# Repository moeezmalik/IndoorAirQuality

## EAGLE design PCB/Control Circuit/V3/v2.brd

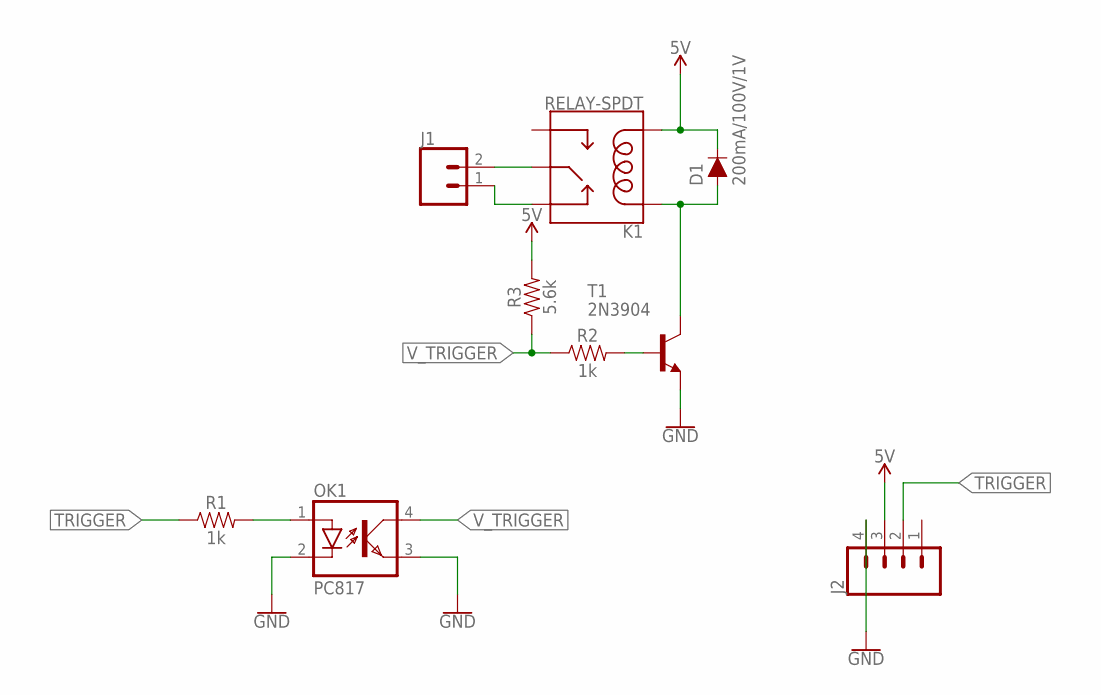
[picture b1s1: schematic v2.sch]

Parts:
D1: 200mA/100V/1V; DIODE-1N4148-KIT
J1: CONN_025MM; SCREWTERMINAL-5MM-2
J2: CONN_04; 1X04
K1: RELAY-SPDT; RELAY_G5LE
OK1: PC817; DIL04
R1, R2: 1k; AXIAL-0.3
R3: 5.6k; AXIAL-0.3
T1: 2N3904; TO92

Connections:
5V: D1.C, J2.3, K1.5 (COIL2), R3.P$2 (2)
GND: J2.4, OK1.2 (C), OK1.3 (EMIT), T1.3 (E)
unnamed: OK1.1 (A), R1.P$2 (2)
unnamed: J1.2, K1.1 (MAIN)
unnamed: J1.1, K1.4 (NC)
unnamed: R2.P$2 (2), T1.2 (B)
unnamed: D1.A, K1.2 (COIL1), T1.1 (C)
TRIGGER: J2.2, R1.P$1 (1)
V_TRIGGER: OK1.4 (COL), R2.P$1 (1), R3.P$1 (1)

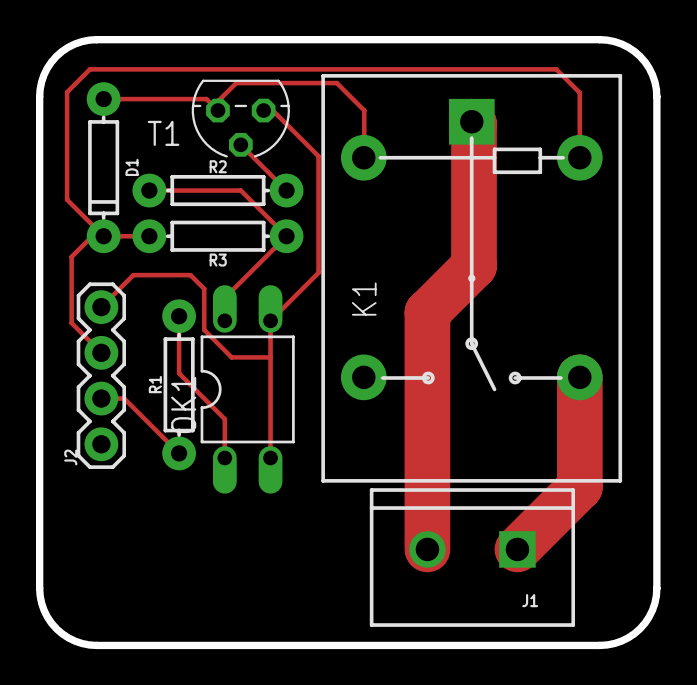
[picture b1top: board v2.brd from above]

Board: 2 copper layers, 34.3 x 33.7 mm, 9 parts (0 on the bottom side), 9 nets.

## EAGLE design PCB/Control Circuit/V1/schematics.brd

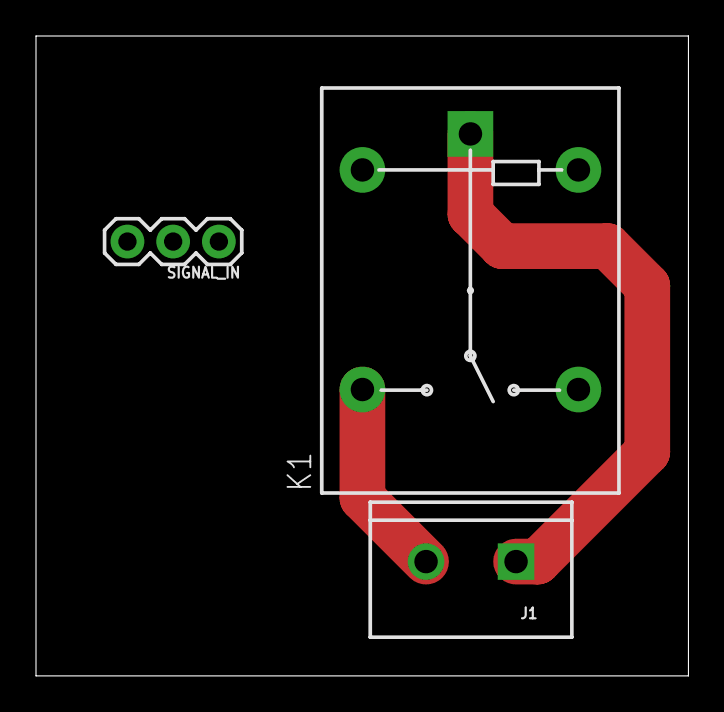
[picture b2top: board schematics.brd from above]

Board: 2 copper layers, 36.2 x 35.5 mm, 3 parts (0 on the bottom side), 3 nets.

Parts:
J1: SCREWTERMINAL-5MM-2
K1: RELAY-SPDT; RELAY_G5LE
SIGNAL_IN: 1X03

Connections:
5V: K1.5, SIGNAL_IN.2
unnamed: J1.2, K1.3
unnamed: J1.1, K1.1

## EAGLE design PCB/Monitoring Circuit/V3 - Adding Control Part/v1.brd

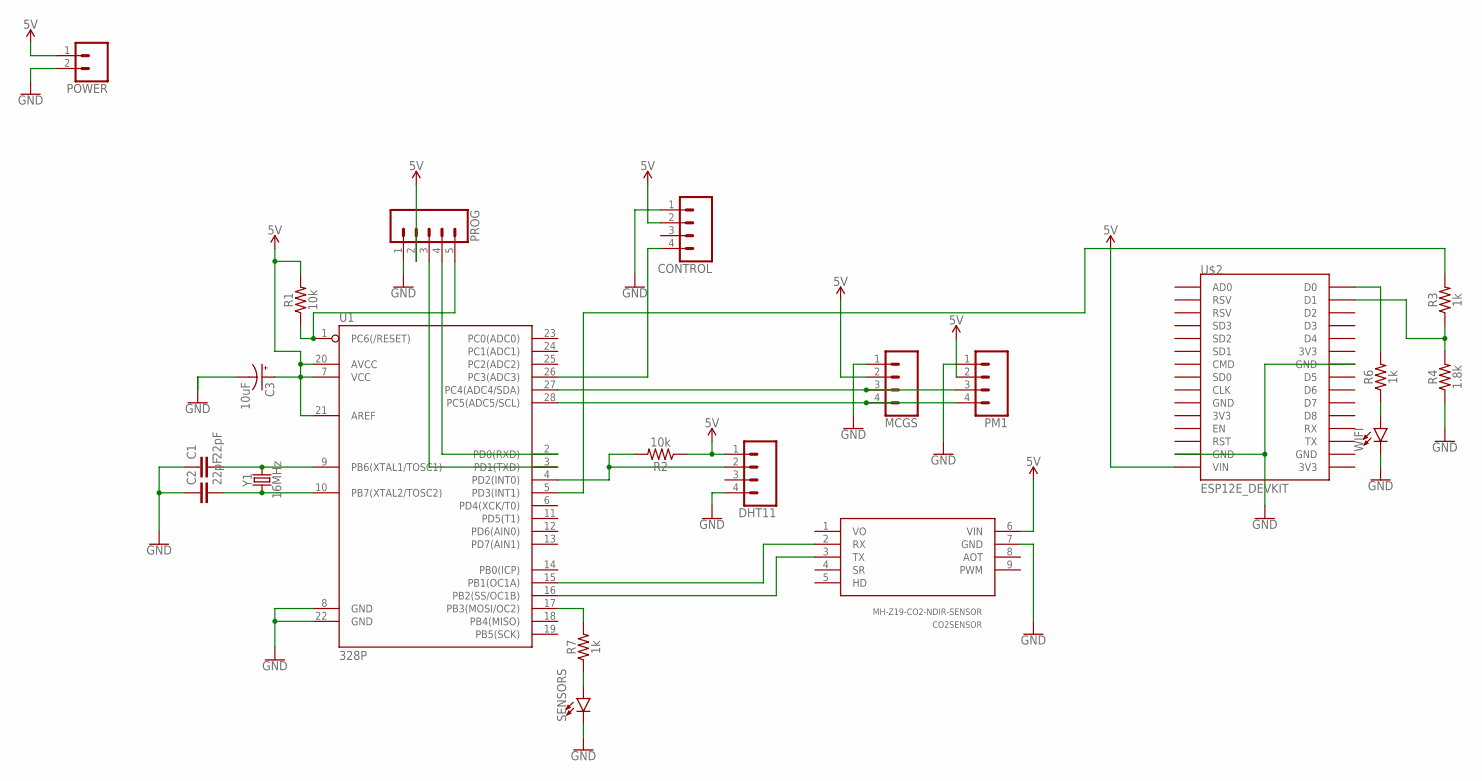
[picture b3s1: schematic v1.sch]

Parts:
C1, C2: 22pF; CAP-PTH-2.54
C3: 10uF; CPOL-RADIAL-2.5MM-5MM
CO2SENSOR: MH-Z19-CO2-NDIR-SENSOR; MH-Z19
CONTROL: CONN_04; 1X04
DHT11: CONN_04; 1X04
MCGS: CONN_04; 1X04
PM1: CONN_04; 1X04
POWER: CONN_02; 1X02
PROG: CONN_05; 1X05
R1, R2: 10k; AXIAL-0.3
R3, R6, R7: 1k; AXIAL-0.3
R4: 1.8k; AXIAL-0.3
SENSORS: LED1206; LED-1206
U1: 328P; DIP28
U$2: ESP12E_DEVKIT
WIFI: LED1206; LED-1206
Y1: 16MHz; HC49US

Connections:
5V: C3.1 (+), CO2SENSOR.6 (VIN), CONTROL.2, DHT11.1, MCGS.2, PM1.2, POWER.1, PROG.2, R1.P$2 (2), R2.P$1 (1), U1.7 (VCC), U1.20 (AVCC), U1.21 (AREF), U$2.VIN
GND: C1.1, C2.1, C3.2 (-), CO2SENSOR.7 (GND), CONTROL.1, DHT11.4, MCGS.1, PM1.1, POWER.2, PROG.1, R4.P$1 (1), SENSORS.C, U1.8 (GND), U1.22 (GND), U$2.GND@1 (GND), U$2.GND@2 (GND), WIFI.C
unnamed: PROG.4, U1.2 (PD0(RXD))
unnamed: PROG.5, R1.P$1 (1), U1.1 (PC6(/RESET))
unnamed: PROG.3, U1.3 (PD1(TXD))
unnamed: C1.2, U1.9 (PB6(XTAL1/TOSC1)), Y1.2
unnamed: C2.2, U1.10 (PB7(XTAL2/TOSC2)), Y1.1
unnamed: CONTROL.4, U1.26 (PC3(ADC3))
unnamed: DHT11.2, R2.P$2 (2), U1.4 (PD2(INT0))
unnamed: MCGS.3, PM1.3, U1.27 (PC4(ADC4/SDA))
unnamed: MCGS.4, PM1.4, U1.28 (PC5(ADC5/SCL))
unnamed: R3.P$2 (2), U1.5 (PD3(INT1))
unnamed: CO2SENSOR.2 (RX), U1.15 (PB1(OC1A))
unnamed: CO2SENSOR.3 (TX), U1.16 (PB2(SS/OC1B))
unnamed: R3.P$1 (1), R4.P$2 (2), U$2.D1
unnamed: R6.P$2 (2), U$2.D0
unnamed: R6.P$1 (1), WIFI.A
unnamed: R7.P$2 (2), U1.17 (PB3(MOSI/OC2))
unnamed: R7.P$1 (1), SENSORS.A
VO: CO2SENSOR.1 (VO)

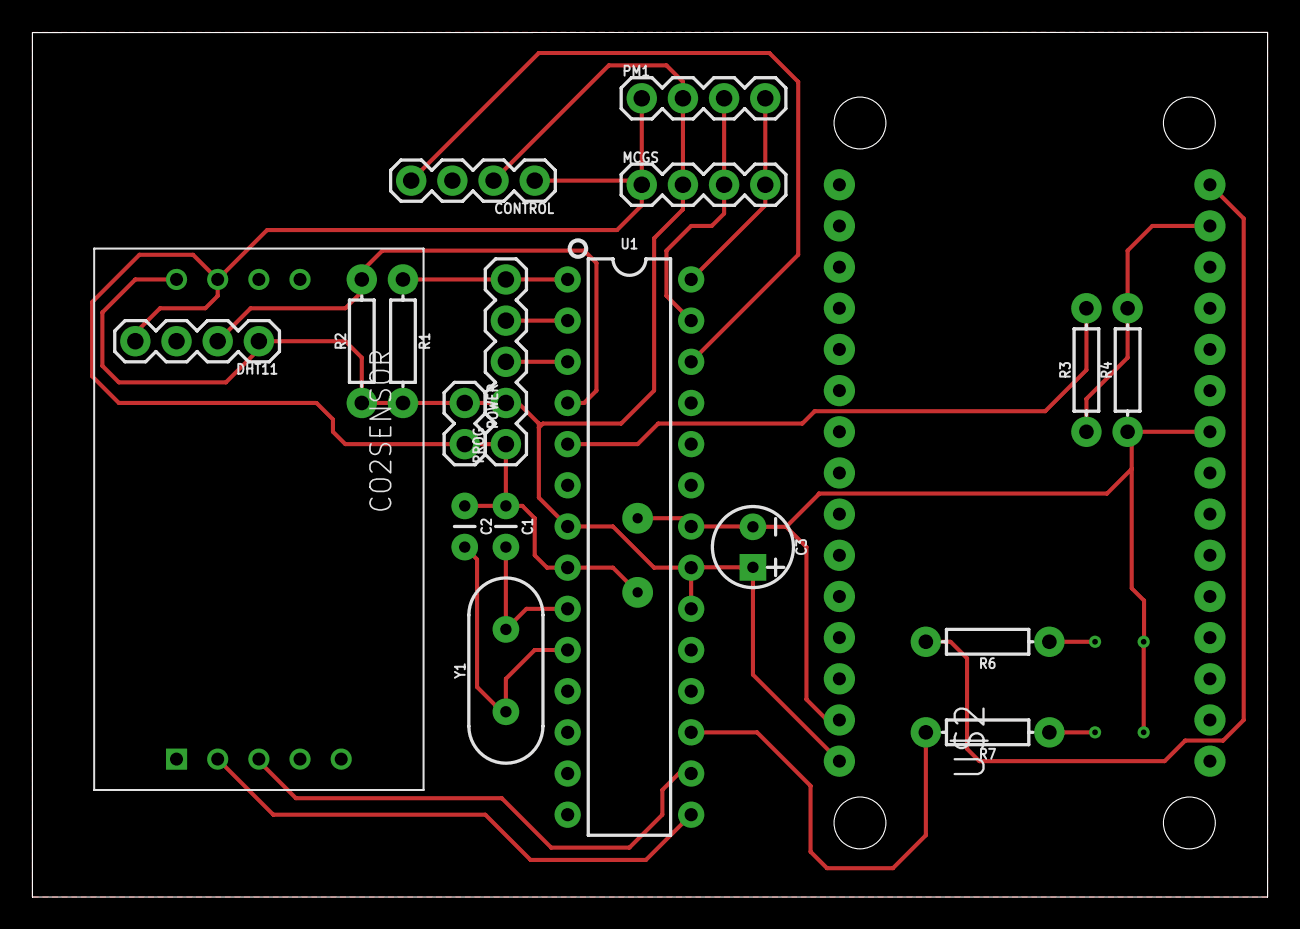
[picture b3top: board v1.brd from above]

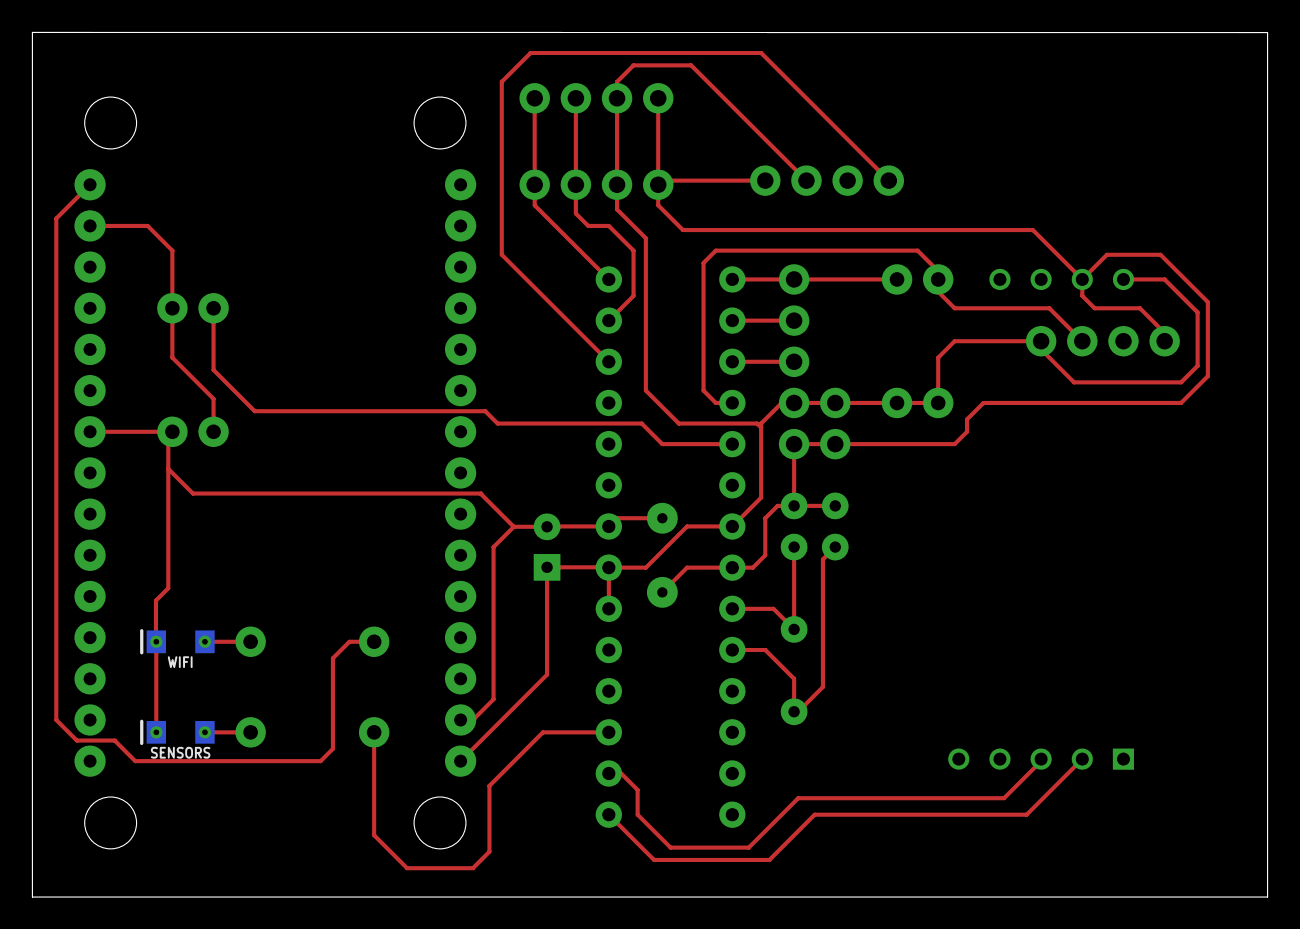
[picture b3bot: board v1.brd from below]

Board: 2 copper layers, 76.2 x 53.3 mm, 21 parts (2 on the bottom side), 19 nets.

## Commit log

2019-11-14 Added Original Files
2019-11-18 Added the control circuit pcb
2019-11-18 Converted image to bw
2019-11-18 added monochrome image for pcb
2019-11-18 Version 3 of monitoring PCB
2019-11-18 Modified monochrom image
2019-11-18 showed vias
2019-11-18 New PCB with control
2019-11-21 Changed the delay to 20 seconds
2019-11-26 Checking control part
2019-11-27 Checking Relay
2019-11-27 MacOS Files
2019-11-27 Defining UART pins, cleaning code.
2019-11-27 Changed WiFi credentials.
2019-11-28 Enclosure file laser cutting of purifier
2019-12-30 Control Circuit v2
2019-12-30 macOS BS
2019-12-30 Fixed the relay not switching circuit
2019-12-31 Made ammendments in PCB and got them print ready
2020-01-02 Control PCB with transistor switcher
2020-01-15 Minor changes

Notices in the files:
parts and their libraries:
SparkFun-Connectors: Licensing: Creative Commons ShareAlike 4.0 International - https://creativecommons.org/licenses/by-sa/4.0
